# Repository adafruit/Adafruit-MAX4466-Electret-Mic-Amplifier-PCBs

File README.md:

# Adafruit MAX4466 Electret Mic Amplifier PCBs
<a href="http://www.adafruit.com/products/1063"><br/>
Click here to purchase one from the Adafruit shop</a>

Add an ear to your project with this well-designed electret microphone amplifier. This fully assembled and tested board comes with a 20-20KHz electret microphone soldered on. For the amplification, we use the Maxim MAX4466, an op-amp specifically designed for this delicate task! The amplifier has excellent power supply noise rejection, so this amplifier sounds really good and isn't nearly as noisy or scratchy as other mic amp breakouts we've tried!

This breakout is best used for projects such as voice changers, audio recording/sampling, and audio-reactive projects that use FFT. On the back, we include a small trimmer pot to adjust the gain. You can set the gain from 25x to 125x. That's down to be about 200mVpp (for normal speaking volume about 6" away) which is good for attaching to something that expects 'line level' input without clipping, or up to about 1Vpp, ideal for reading from a microcontroller ADC. The output is rail-to-rail so if the sounds gets loud, the output can go up to 5Vpp!

PCB files for Adafruit MAX4466 Electret Mic Amplifier. The format is EagleCAD schematic and board layout

For more details, check out the product page at https://www.adafruit.com/products/1063

### License

Adafruit invests time and resources providing this open source design, please support Adafruit and open-source hardware by purchasing products from [Adafruit](https://www.adafruit.com)!

All text above must be included in any redistribution

Designed by Limor Fried/Ladyada for Adafruit Industries.
Creative Commons Attribution/Share-Alike, all text above must be included in any redistribution. 
See license.txt for additional information.

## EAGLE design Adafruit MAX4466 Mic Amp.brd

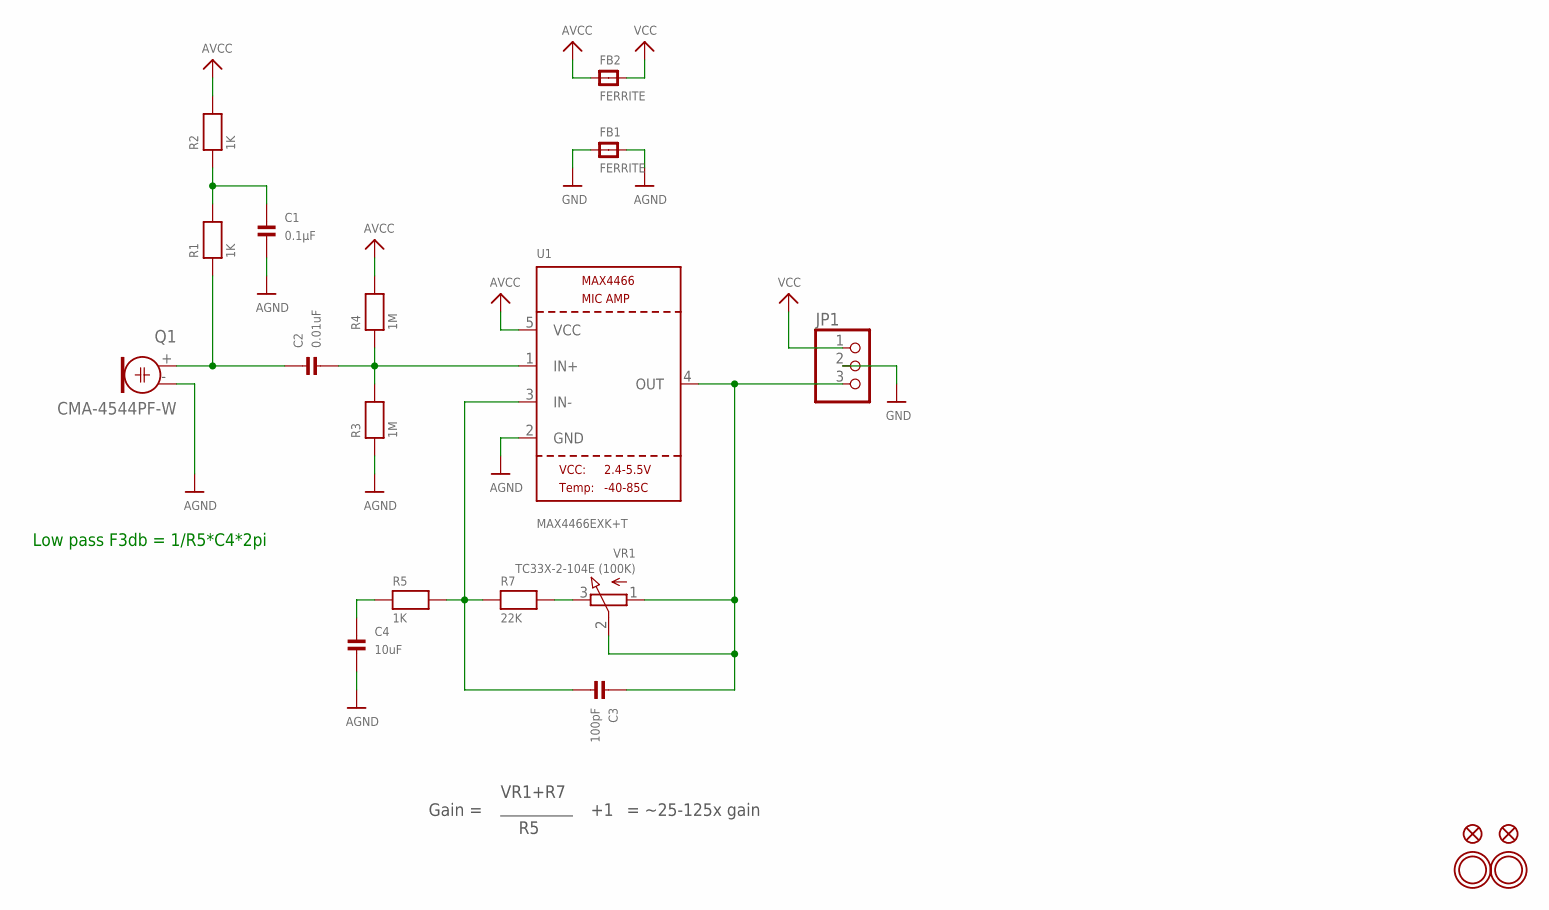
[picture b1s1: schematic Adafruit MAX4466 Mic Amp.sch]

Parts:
C1: 0.1µF; 0805
C2: 0.01uF; 0805
C3: 100pF; 0805
C4: 10uF; 0805
FB1, FB2: FERRITE; 0805
FID1, FID2: FIDUCIAL""; FIDUCIAL_1MM
JP1: HEADER-1X376MIL; 1X03_ROUND_76
Q1: CMA-4544PF-W; ELECTRET_9.7
R1, R2, R5: 1K; 0805
R3, R4: 1M; 0805
R7: 22K; 0805
U1: MAX4466EXK+T; SC70-5
U$11, U$14: MOUNTINGHOLE2.5; MOUNTINGHOLE_2.5_PLATED
VR1: TC33X-2-104E (100K); TRIMPOT_BOURNS_TC33X-2

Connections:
AGND: C1.2, C4.2, FB1.2, Q1.- (1), R3.1, U1.2 (GND)
AVCC: FB2.1, R2.2, R4.2, U1.5 (VCC)
GND: FB1.1, JP1.2
unnamed: C3.2, R5.2, R7.1, U1.3 (IN-)
unnamed: R7.2, VR1.3 (E)
unnamed: C2.1, Q1.+ (2), R1.1
unnamed: C1.1, R1.2, R2.1
unnamed: C2.2, R3.2, R4.1, U1.1 (IN+)
unnamed: C3.1, JP1.3, U1.4 (OUT), VR1.1 (A), VR1.2 (S)
unnamed: C4.1, R5.1
VCC: FB2.2, JP1.1

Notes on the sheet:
Gain =
VR1+R7
= ~25-125x gain
Low pass F3db = 1/R5*C4*2pi

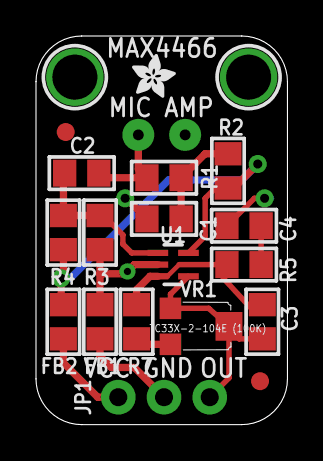
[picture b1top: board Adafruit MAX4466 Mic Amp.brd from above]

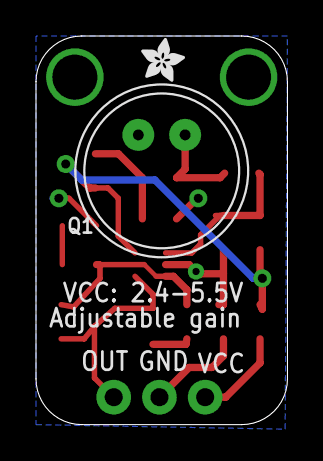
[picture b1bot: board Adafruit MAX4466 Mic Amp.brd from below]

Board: 2 copper layers, 14.0 x 21.6 mm, 22 parts (2 on the bottom side), 11 nets.

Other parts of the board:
U$16, U$17: ADAFRUIT_2.5MM

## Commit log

2014-09-23 init

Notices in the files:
parts and their libraries:
microbuilder: This work is placed in the public domain, and may be freely used for commercial and non-commercial work with the following conditions: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
